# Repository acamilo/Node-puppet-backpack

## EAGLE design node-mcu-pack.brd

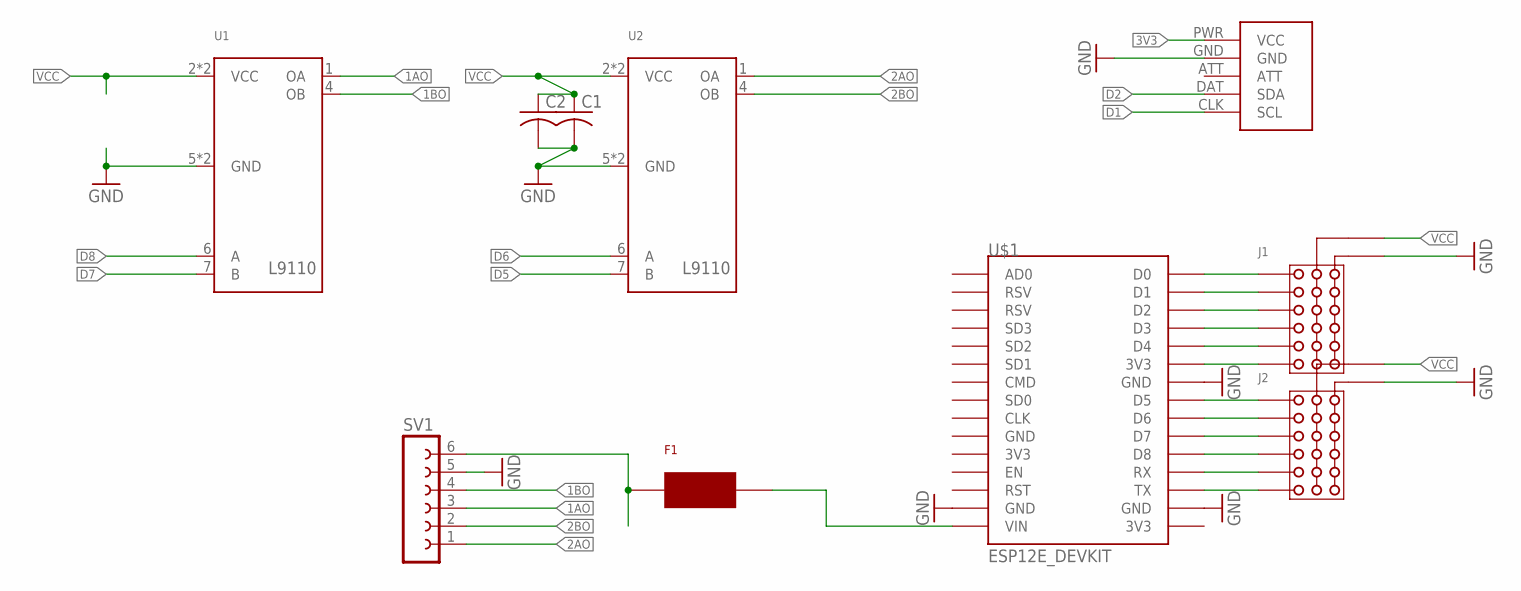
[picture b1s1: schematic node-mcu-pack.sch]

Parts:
C1, C2: C-USC0805; C0805
F1: 0154
J1, J2: IOBLOCK6; IOBLOCK100MILX6
SV1: FE06-1; FE06
U1, U2: L9110SMT; 8S1
U$1: ESP12E_DEVKIT
U$2: WIICHUCKOUTIE; CHUCK-OUTIE

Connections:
1AO: SV1.3, U1.1 (OA)
1BO: SV1.4, U1.4 (OB)
2AO: SV1.1, U2.1 (OA)
2BO: SV1.2, U2.4 (OB)
3V3: J1.P$6, U$1.3V3@1 (3V3), U$2.PWR (VCC)
D0: J1.P$1, U$1.D0
D1: J1.P$2, U$1.D1, U$2.CLK (SCL)
D2: J1.P$3, U$1.D2, U$2.DAT (SDA)
D5: J2.P$1, U2.7 (B), U$1.D5
D6: J2.P$2, U2.6 (A), U$1.D6
D7: J2.P$3, U1.7 (B), U$1.D7
D8: J2.P$4, U1.6 (A), U$1.D8
GND: C1.2, C2.2, J1.G1, J1.G2, J1.G3, J1.G4, J1.G5, J1.G6, J2.G1, J2.G2, J2.G3, J2.G4, J2.G5, J2.G6, SV1.5, U1.5 (GND), U1.8 (GND), U2.5 (GND), U2.8 (GND), U$1.GND@1 (GND), U$1.GND@2 (GND), U$1.GND@3 (GND), U$2.GND
unnamed: F1.1, SV1.6
unnamed: J2.P$6, U$1.TX
unnamed: J2.P$5, U$1.RX
unnamed: J1.P$5, U$1.D4
unnamed: J1.P$4, U$1.D3
VCC: C1.1, C2.1, F1.2, J1.P1, J1.P2, J1.P3, J1.P4, J1.P5, J1.P6, J2.P1, J2.P2, J2.P3, J2.P4, J2.P5, J2.P6, U1.2 (VCC), U1.3 (VCC), U2.2 (VCC), U2.3 (VCC), U$1.VIN

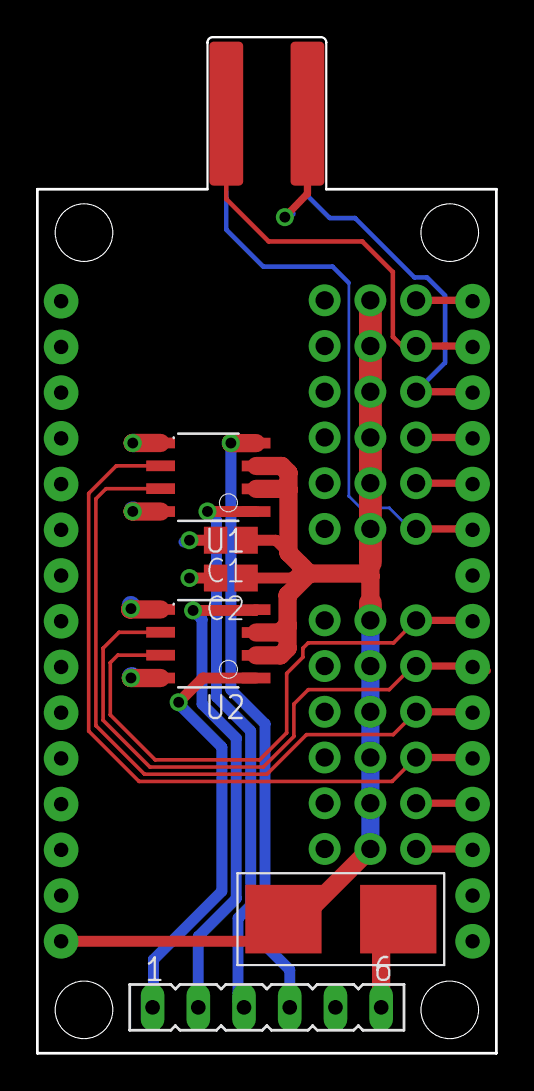
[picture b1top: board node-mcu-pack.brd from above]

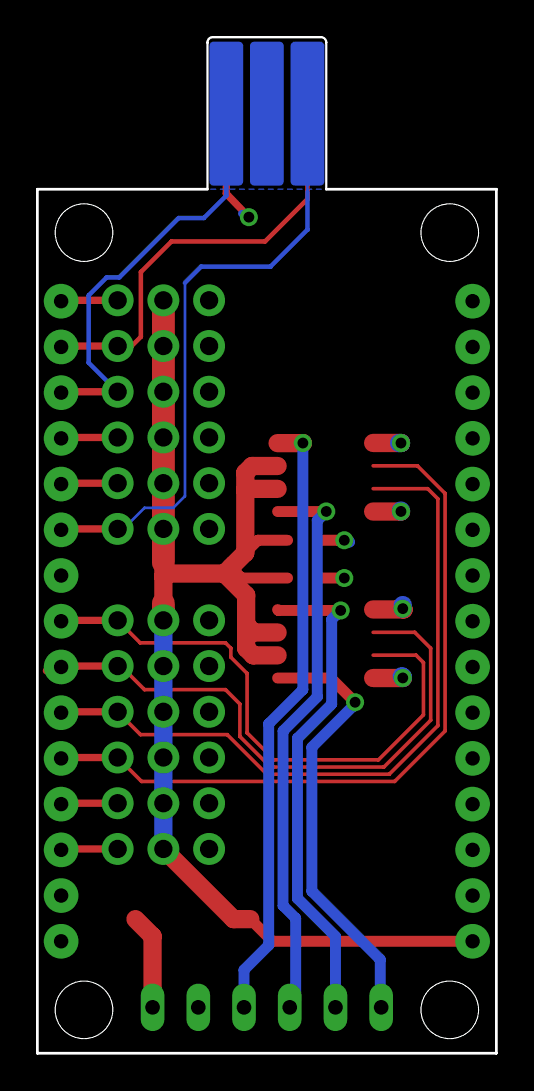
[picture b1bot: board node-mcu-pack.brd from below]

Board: 2 copper layers, 25.5 x 56.4 mm, 10 parts (2 on the bottom side), 19 nets.

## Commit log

2016-10-29 committed PCB
2016-11-01 schematic img
2016-11-03 moved i2c pins for wiicuck
2017-01-16 working in single sided board
